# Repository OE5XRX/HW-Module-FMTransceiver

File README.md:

# HW-Module-Template

## Description

This repository is a template for hardware modules using KiCad, designed for clean, maintainable development with CI/CD pipelines generating and publishing production data automatically.

## Features
* Structured KiCad project (schematic, PCB)
* Clean repository: no production data stored
* GitHub Actions CI/CD pipeline:
  * Generates Gerber, BOM, and assembly files
  * Uploads artifacts to GitHub Releases
* Open Hardware license ready (CERN-OHL-S)

## Repository Structure

```
HW-Module-Template/
├── .github/workflows/     # CI/CD pipeline scripts
├── doc/                   # Documentation exports
├── symbols/               # Local symbol library (if needed)
├── footprints/            # Local footprint library (if needed)
├── 3d-models/             # STEP/WRL files (optional)
├── main.kicad_pro         # KiCad main project file
├── main.kicad_sch         # KiCad main schematic file
├── main.kicad_pcb         # KiCad main pcb file
├── *.kicad_sch            # other KiCad schematic files
├── LICENSE
└── README.md
```

## Usage
1. Click “Use this template” on GitHub.
2. Clone your repository locally and open in KiCad.
3. fix the missing names in the readme and add documentation in the `doc/index.md` file.
4. Work on your schematic and PCB as usual (create a new project (main-file must be called `main.kicad_*`) or copy a new one into the folder structure).
5. Push your changes.
6. CI/CD will automatically generate production files.
7. If there is a release defined, CI/CD will create a documentation on the main webpage.

## License

This project is licensed under [CERN-OHL-S-2.0](https://choosealicense.com/licenses/cern-ohl-s-2.0/).

## Badges

<br>
<br>
<br>
<br>
<br>

## Contact

OE5XRX Amateur Radio Club<br>
🌐 https://oe5xrx.org<br>
✉️ info@oe5xrx.org<br>

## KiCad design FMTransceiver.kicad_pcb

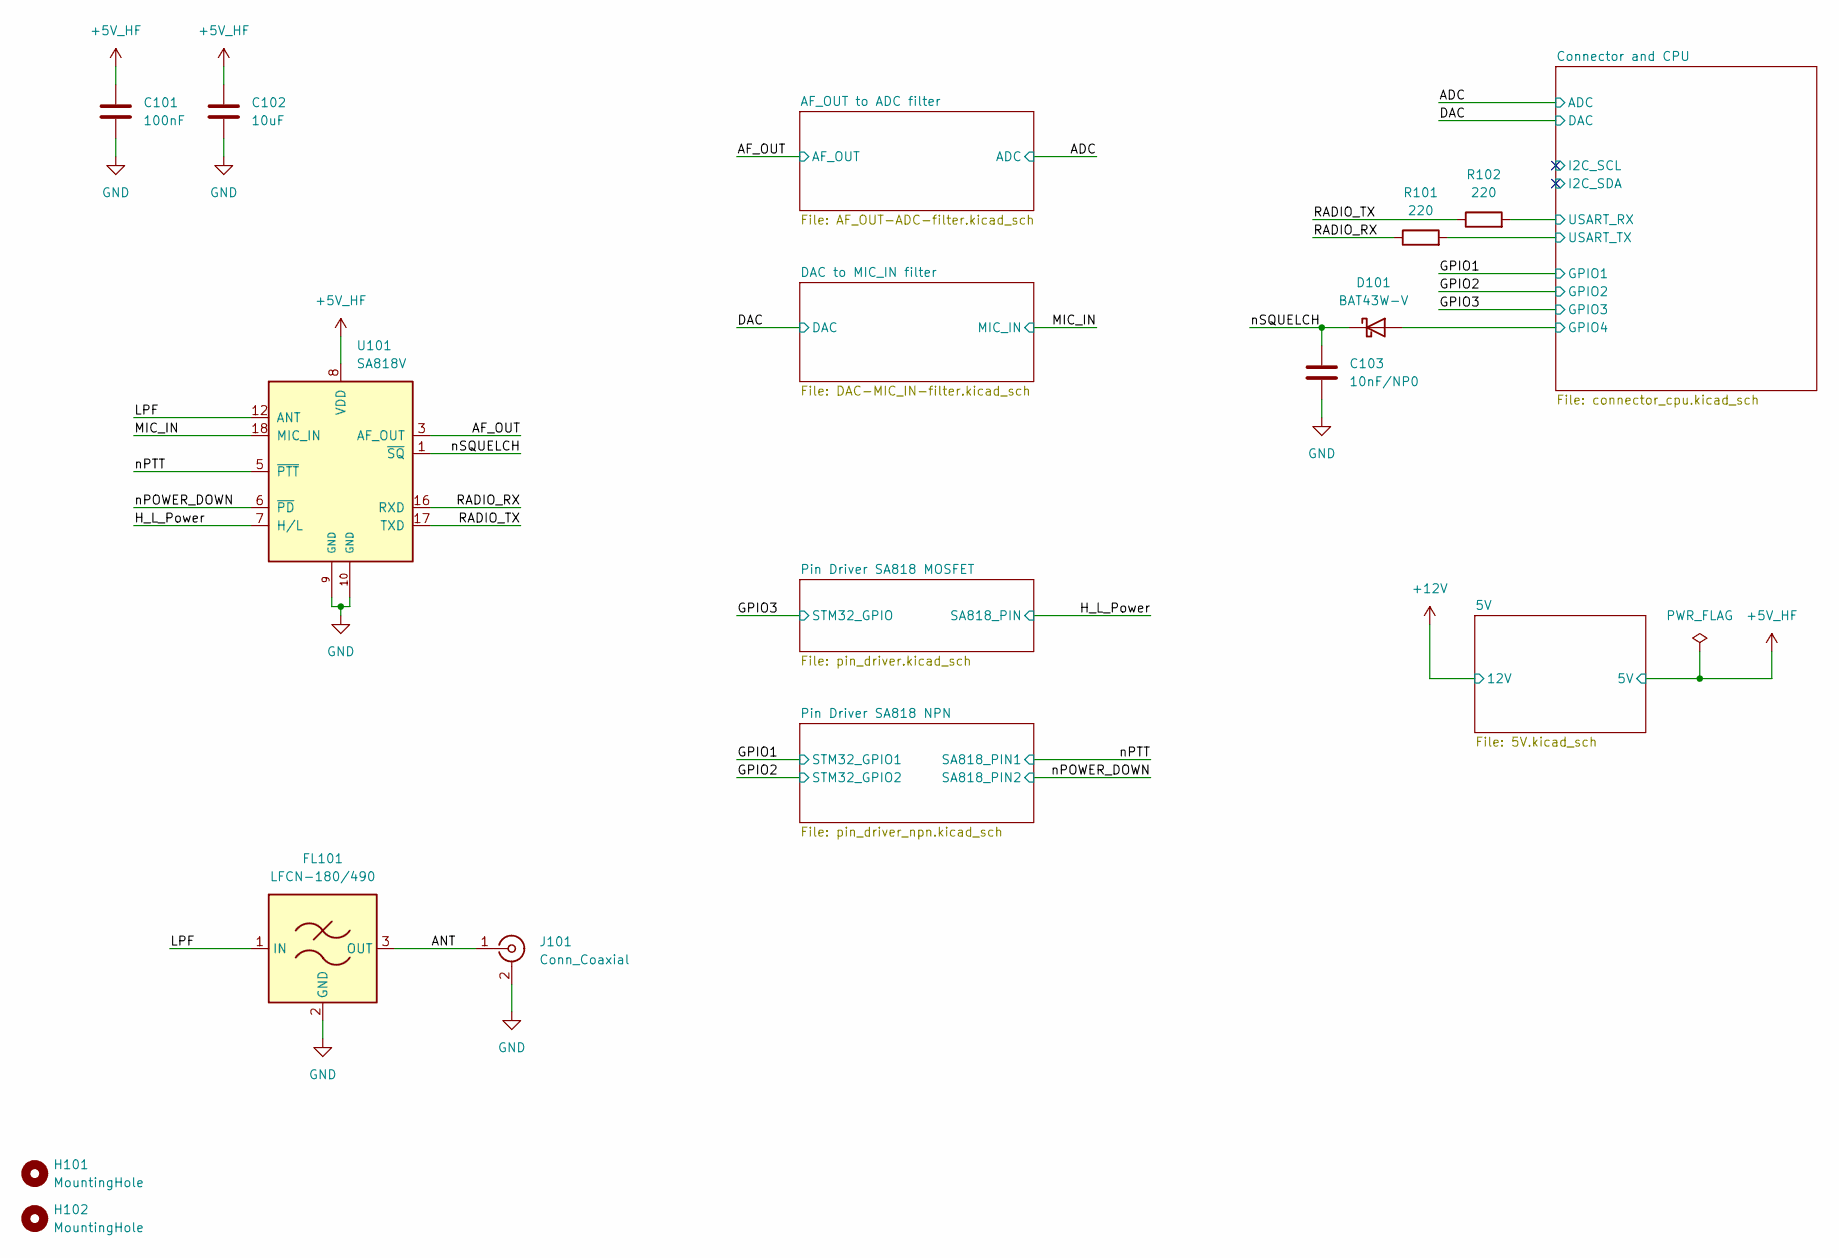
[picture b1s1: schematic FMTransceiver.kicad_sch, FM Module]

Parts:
C101: 100nF; C_0805_2012Metric; LCSC C28233
C102: 10uF; C_0805_2012Metric; MOUSER 963-EMK212BJ106KG-T
C103: 10nF/NP0; C_0805_2012Metric; MOUSER 81-GRM2165C2A103JA1D
D101: BAT43W-V; D_SOD-123; MOUSER 78-BAT43W-G3-08
FL101: LFCN-180/490; Filter_Mini-Circuits_FV1206; MOUSER 139-LFCN-180,139-LFCN-490
H101, H102: MountingHole; MountingHole_3.2mm_M3
J101: Conn_Coaxial; SMA_Amphenol_132289_EdgeMount; MOUSER 530-142-0701-801
R101, R102: 220; R_0805_2012Metric; MOUSER 667-ERA-6AEB221V
U101: SA818V; DRA818; LCSC C3001504

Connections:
+5V_HF: C101.2, C102.2, U101.8 (VDD); also elsewhere on the board
/AF_OUT: U101.3 (AF_OUT); also elsewhere on the board
/ANT: FL101.3 (OUT), J101.1 (In)
/Connector and CPU/GPIO4: D101.2 (A); also elsewhere on the board
/Connector and CPU/USART_RX: R102.2; also elsewhere on the board
/Connector and CPU/USART_TX: R101.2; also elsewhere on the board
/H_L_Power: U101.7 (H/L); also elsewhere on the board
/LPF: FL101.1 (IN), U101.12 (ANT)
/MIC_IN: U101.18 (MIC_IN); also elsewhere on the board
/RADIO_RX: R101.1, U101.16 (RXD)
/RADIO_TX: R102.1, U101.17 (TXD)
/nPOWER_DOWN: U101.6 (~PD); also elsewhere on the board
/nPTT: U101.5 (~PTT); also elsewhere on the board
/nSQUELCH: C103.2, D101.1 (K), U101.1 (~SQ)
GND: C101.1, C102.1, C103.1, FL101.2 (GND), FL101.4 (GND), J101.2 (Ext), U101.9 (GND), U101.10 (GND); also elsewhere on the board

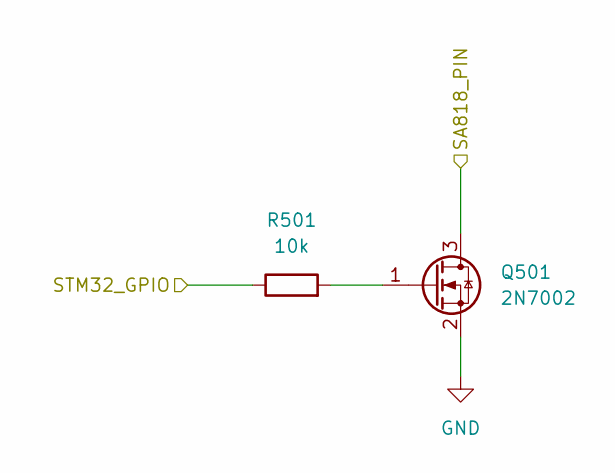
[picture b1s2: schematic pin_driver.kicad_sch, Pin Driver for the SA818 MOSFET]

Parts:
Q501: 2N7002; SOT-23; MOUSER 637-2N7002
R501: 10k; R_0805_2012Metric; MOUSER 603-RT0805DRE0710KL

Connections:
/GPIO3: R501.1; also elsewhere on the board
/H_L_Power: Q501.3 (D); also elsewhere on the board
GND: Q501.2 (S); also elsewhere on the board
unnamed: Q501.1 (G), R501.2

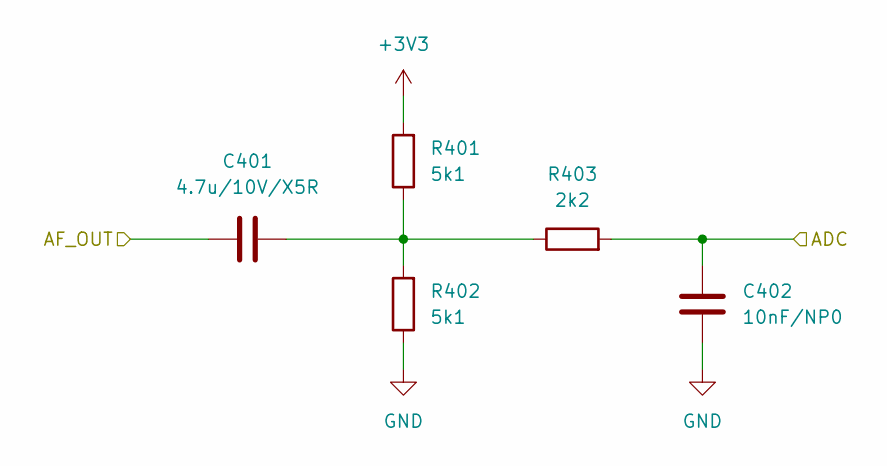
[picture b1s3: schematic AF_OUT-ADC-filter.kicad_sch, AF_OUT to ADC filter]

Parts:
C401: 4.7u/10V/X5R; C_0805_2012Metric; MOUSER 187-CL21A475KAQNNNF
C402: 10nF/NP0; C_0805_2012Metric; MOUSER 81-GRM2165C2A103JA1D
R401, R402: 5k1; R_0805_2012Metric; LCSC C27834
R403: 2k2; R_0805_2012Metric; LCSC C17520

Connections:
+3V3: R401.2; also elsewhere on the board
/ADC: C402.2, R403.2; also elsewhere on the board
/AF_OUT: C401.2; also elsewhere on the board
GND: C402.1, R402.1; also elsewhere on the board
unnamed: C401.1, R401.1, R402.2, R403.1

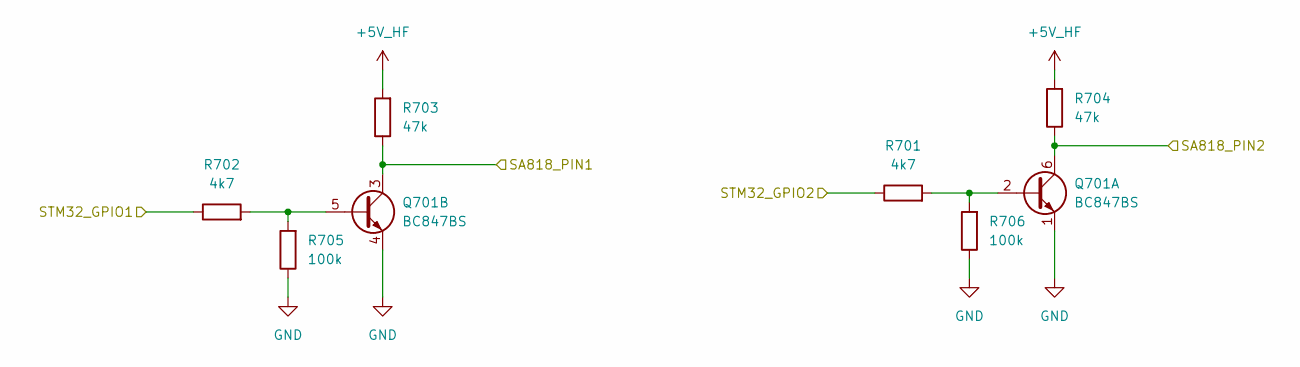
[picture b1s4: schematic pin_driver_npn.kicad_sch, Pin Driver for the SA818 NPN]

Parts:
Q701: BC847BS; SOT-363_SC-70-6; MOUSER 241-BC847BS_R1_00001
R701, R702: 4k7; R_0805_2012Metric; MOUSER 603-RC0805FR-074K7L
R703, R704: 47k; R_0805_2012Metric; MOUSER 603-AC0805FR-1047KL
R705, R706: 100k; R_0805_2012Metric; MOUSER 603-RC0805JR-07100KL

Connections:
+5V_HF: R703.2, R704.2; also elsewhere on the board
/GPIO1: R702.1; also elsewhere on the board
/GPIO2: R701.1; also elsewhere on the board
/nPOWER_DOWN: Q701.6 (C1), R704.1; also elsewhere on the board
/nPTT: Q701.3 (C2), R703.1; also elsewhere on the board
GND: Q701.1 (E1), Q701.4 (E2), R705.1, R706.1; also elsewhere on the board
unnamed: Q701.2 (B1), R701.2, R706.2
unnamed: Q701.5 (B2), R702.2, R705.2

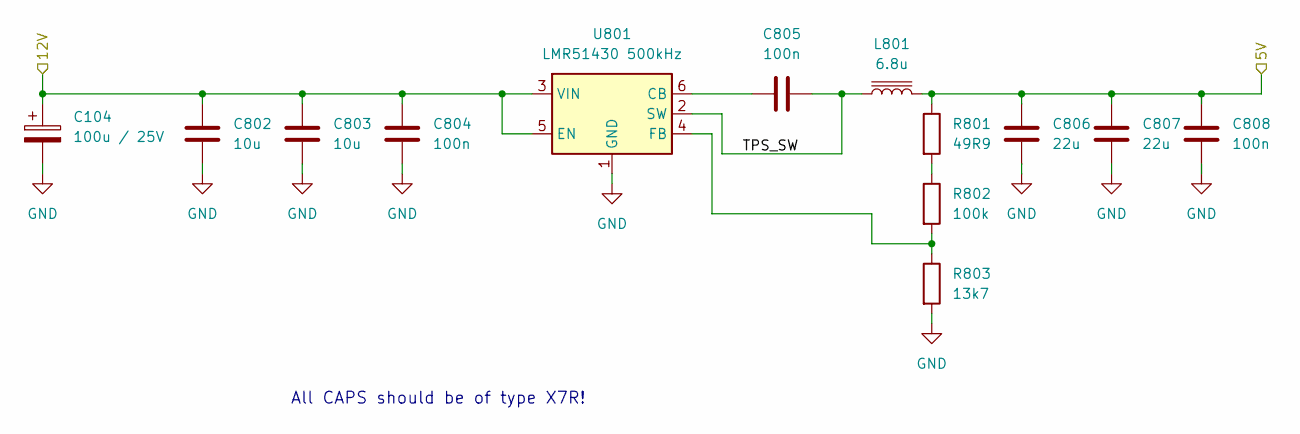
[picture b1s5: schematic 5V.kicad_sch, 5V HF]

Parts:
C104: 100u / 25V; CP_EIA-7343-43_Kemet-X; LCSC C132558
C802, C803: 10u; C_1206_3216Metric; LCSC C13585
C804, C805, C808: 100n; C_0805_2012Metric; LCSC C28233
C806, C807: 22u; C_1206_3216Metric; LCSC C12891
L801: 6.8u; WE-XHMI_6060; MOUSER 710-74439346068
R801: 49R9; R_0805_2012Metric; MOUSER 667-ERA-6AED49R9V
R802: 100k; R_0805_2012Metric; MOUSER 603-RC0805JR-07100KL
R803: 13k7; R_0805_2012Metric; MOUSER 652-CR0805FX-1372ELF
U801: LMR51430 500kHz; SOT-23-6; MOUSER 595-LMR51430XDDCR

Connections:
+5V_HF: C806.2, C807.2, C808.2, L801.2, R801.1; also elsewhere on the board
+12V: C104.1, C802.1, C803.1, C804.1, U801.3 (VIN), U801.5 (EN); also elsewhere on the board
/5V/TPS_SW: C805.2, L801.1, U801.2 (SW)
GND: C104.2, C802.2, C803.2, C804.2, C806.1, C807.1, C808.1, R803.2, U801.1 (GND); also elsewhere on the board
unnamed: R801.2, R802.1
unnamed: C805.1, U801.6 (CB)
unnamed: R802.2, R803.1, U801.4 (FB)

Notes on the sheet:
All CAPS should be of type X7R!

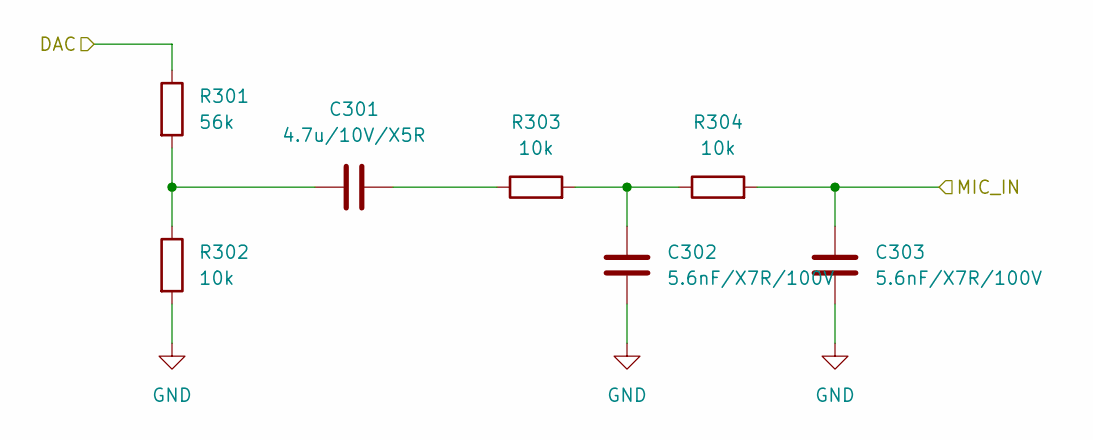
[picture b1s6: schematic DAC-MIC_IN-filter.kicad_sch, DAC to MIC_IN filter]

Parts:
C301: 4.7u/10V/X5R; C_0805_2012Metric; MOUSER 187-CL21A475KAQNNNF
C302, C303: 5.6nF/X7R/100V; C_0805_2012Metric; MOUSER 791-0805B562K201CT
R301: 56k; R_0805_2012Metric; MOUSER 603-RT0805DRE0756KL
R302, R303, R304: 10k; R_0805_2012Metric; MOUSER 603-RT0805DRE0710KL

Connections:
/DAC: R301.1; also elsewhere on the board
/MIC_IN: C303.1, R304.2; also elsewhere on the board
GND: C302.2, C303.2, R302.2; also elsewhere on the board
unnamed: C301.1, R303.1
unnamed: C301.2, R301.2, R302.1
unnamed: C302.1, R303.2, R304.1

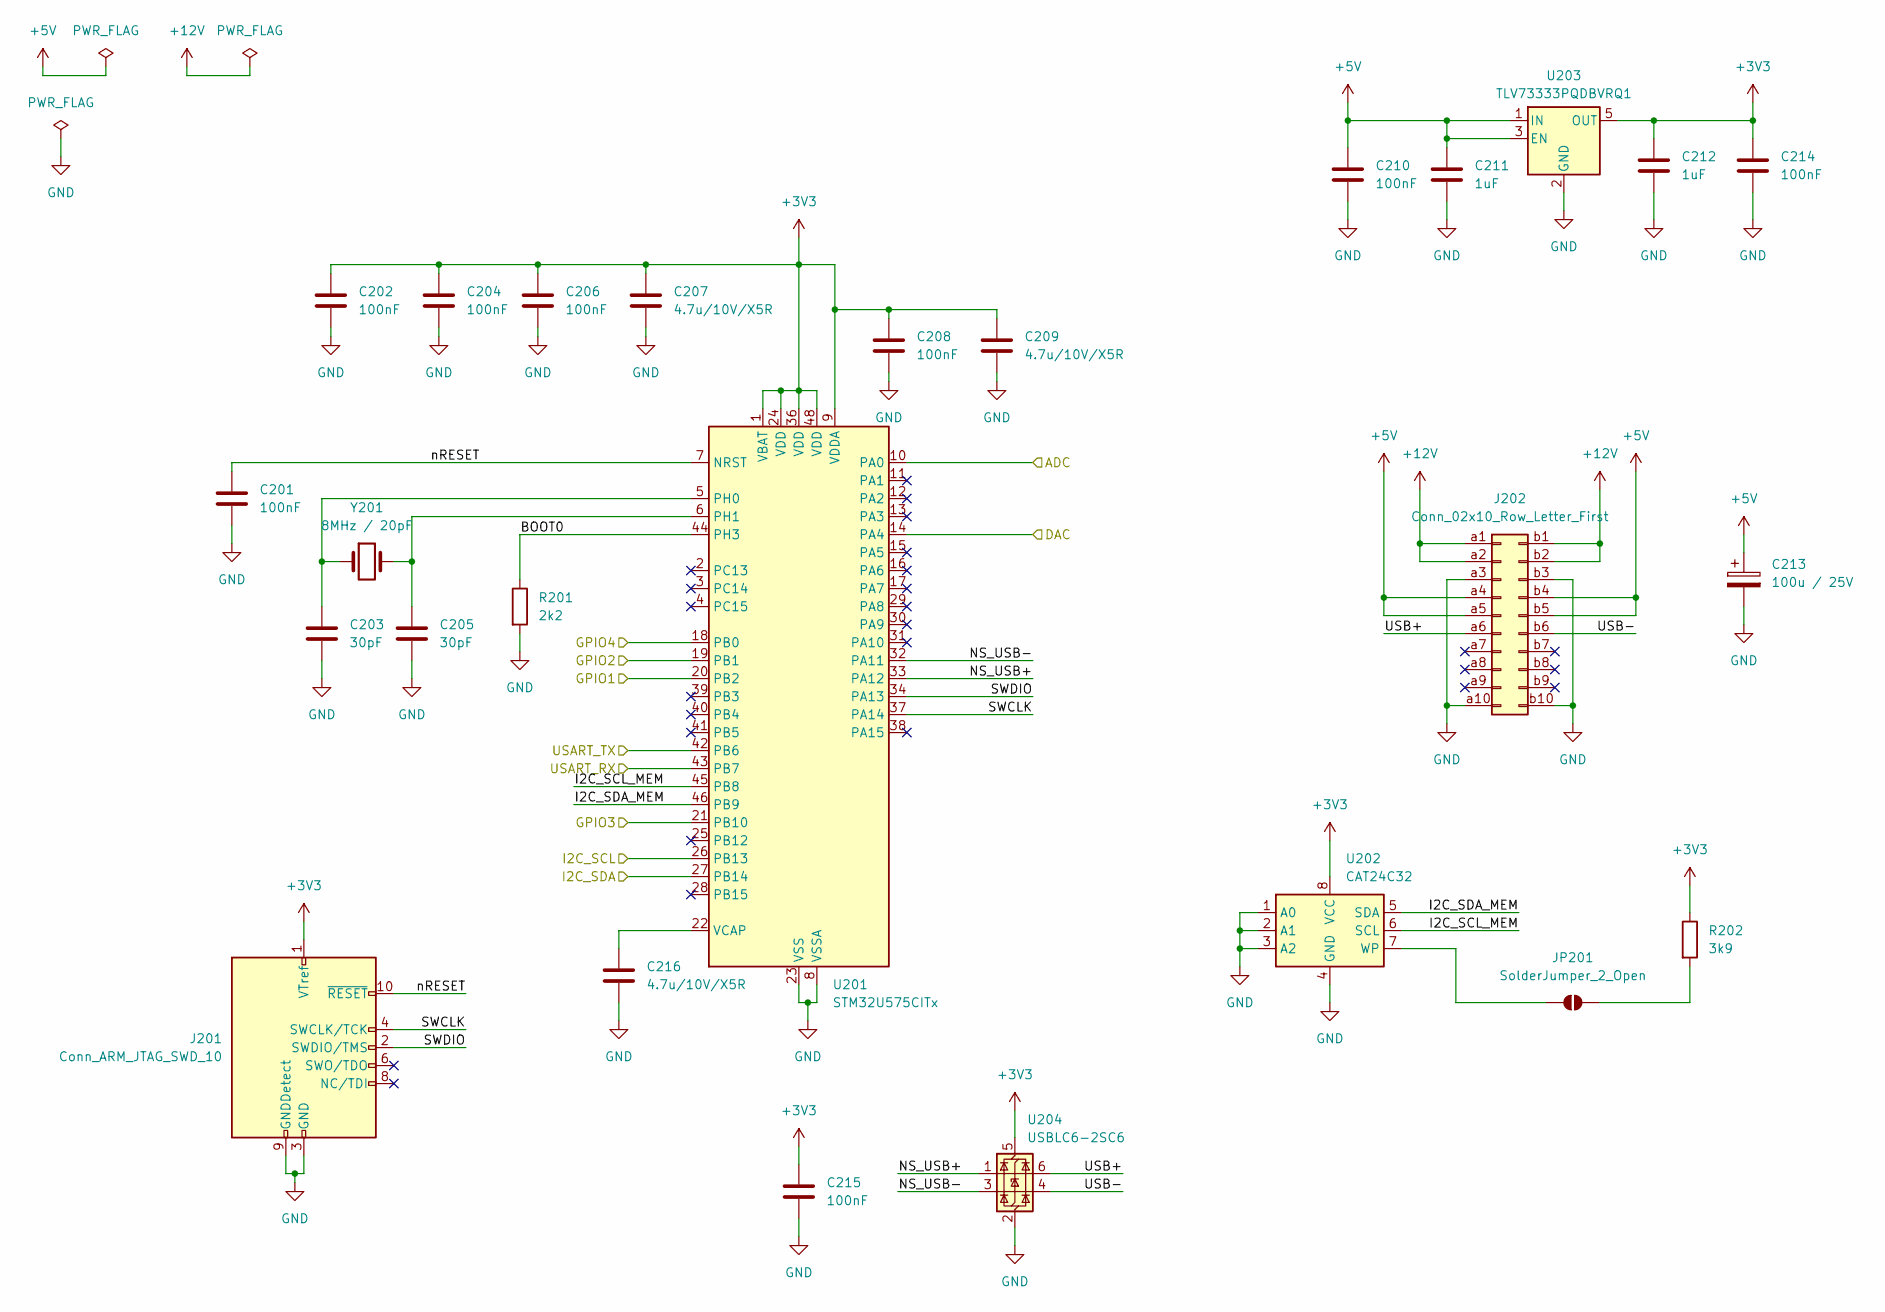
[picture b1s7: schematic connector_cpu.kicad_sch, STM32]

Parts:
C201, C202, C204, C206, C208, C210, C214, C215: 100nF; C_0805_2012Metric; LCSC C28233
C203, C205: 30pF; C_0805_2012Metric; MOUSER 791-0805N300J500CT
C207, C209, C216: 4.7u/10V/X5R; C_0805_2012Metric; MOUSER 187-CL21A475KAQNNNF
C211, C212: 1uF; C_0805_2012Metric; MOUSER 791-0805B105K250CT
C213: 100u / 25V; CP_EIA-7343-43_Kemet-X; LCSC C132558
J201: Conn_ARM_JTAG_SWD_10; PinHeader_2x05_P2.54mm_Horizontal
J202: Conn_02x10_Row_Letter_First; PCN10C-20S-2.54DS; MOUSER 798-PCN10C20S254DS72
JP201: SolderJumper_2_Open; SolderJumper-2_P1.3mm_Open_RoundedPad1.0x1.5mm
R201: 2k2; R_0805_2012Metric; LCSC C17520
R202: 3k9; R_0805_2012Metric; MOUSER 603-RT0805DRD073K9L
U201: STM32U575CITx; LQFP-48_7x7mm_P0.5mm; MOUSER 511-STM32U575CIT6
U202: CAT24C32; SOIC-8_3.9x4.9mm_P1.27mm; MOUSER 698-CAT24C32WI-GT3
U203: TLV73333PQDBVRQ1; SOT-23-5; LCSC C2862550
U204: USBLC6-2SC6; SOT-23-6; LCSC C2827654
Y201: 8MHz / 20pF; Crystal_SMD_HC49-SD; MOUSER 73-XT49M800-20

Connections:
+3V3: C202.2, C204.2, C206.2, C207.2, C208.2, C209.2, C212.1, C214.2, C215.1, J201.1 (VTref), R202.1, U201.1 (VBAT), U201.9 (VDDA), U201.24 (VDD), U201.36 (VDD), U201.48 (VDD), U202.8 (VCC), U203.5 (OUT), U204.5 (VBUS); also elsewhere on the board
+5V: C210.2, C211.1, C213.1, J202.a4, J202.a5, J202.b4, J202.b5, U203.1 (IN), U203.3 (EN)
+12V: J202.a1, J202.a2, J202.b1, J202.b2; also elsewhere on the board
/ADC: U201.10 (PA0); also elsewhere on the board
/Connector and CPU/BOOT0: R201.1, U201.44 (PH3)
/Connector and CPU/GPIO4: U201.18 (PB0); also elsewhere on the board
/Connector and CPU/I2C_SCL: U201.26 (PB13)
/Connector and CPU/I2C_SCL_MEM: U201.45 (PB8), U202.6 (SCL)
/Connector and CPU/I2C_SDA: U201.27 (PB14)
/Connector and CPU/I2C_SDA_MEM: U201.46 (PB9), U202.5 (SDA)
/Connector and CPU/NS_USB+: U201.33 (PA12), U204.1 (I/O1)
/Connector and CPU/NS_USB-: U201.32 (PA11), U204.3 (I/O2)
/Connector and CPU/SWCLK: J201.4 (SWCLK/TCK), U201.37 (PA14)
/Connector and CPU/SWDIO: J201.2 (SWDIO/TMS), U201.34 (PA13)
/Connector and CPU/USART_RX: U201.43 (PB7); also elsewhere on the board
/Connector and CPU/USART_TX: U201.42 (PB6); also elsewhere on the board
/Connector and CPU/USB+: J202.a6, U204.6 (I/O1)
/Connector and CPU/USB-: J202.b6, U204.4 (I/O2)
/Connector and CPU/nRESET: C201.1, J201.10 (~RESET), U201.7 (NRST)
/DAC: U201.14 (PA4); also elsewhere on the board
/GPIO1: U201.20 (PB2); also elsewhere on the board
/GPIO2: U201.19 (PB1); also elsewhere on the board
/GPIO3: U201.21 (PB10); also elsewhere on the board
GND: C201.2, C202.1, C203.2, C204.1, C205.2, C206.1, C207.1, C208.1, C209.1, C210.1, C211.2, C212.2, C213.2, C214.1, C215.2, C216.1, J201.3 (GND), J201.5 (GND), J201.9 (GNDDetect), J202.a3, J202.a10, J202.b3, J202.b10, R201.2, U201.8 (VSSA), U201.23 (VSS), U201.35 (VSS), U201.47 (VSS), U202.1 (A0), U202.2 (A1), U202.3 (A2), U202.4 (GND), U203.2 (GND), U204.2 (GND); also elsewhere on the board
unnamed: JP201.1 (A), U202.7 (WP)
unnamed: JP201.2 (B), R202.2
unnamed: C203.1, U201.5 (PH0), Y201.1
unnamed: C205.1, U201.6 (PH1), Y201.2
unnamed: C216.2, U201.22 (VCAP)

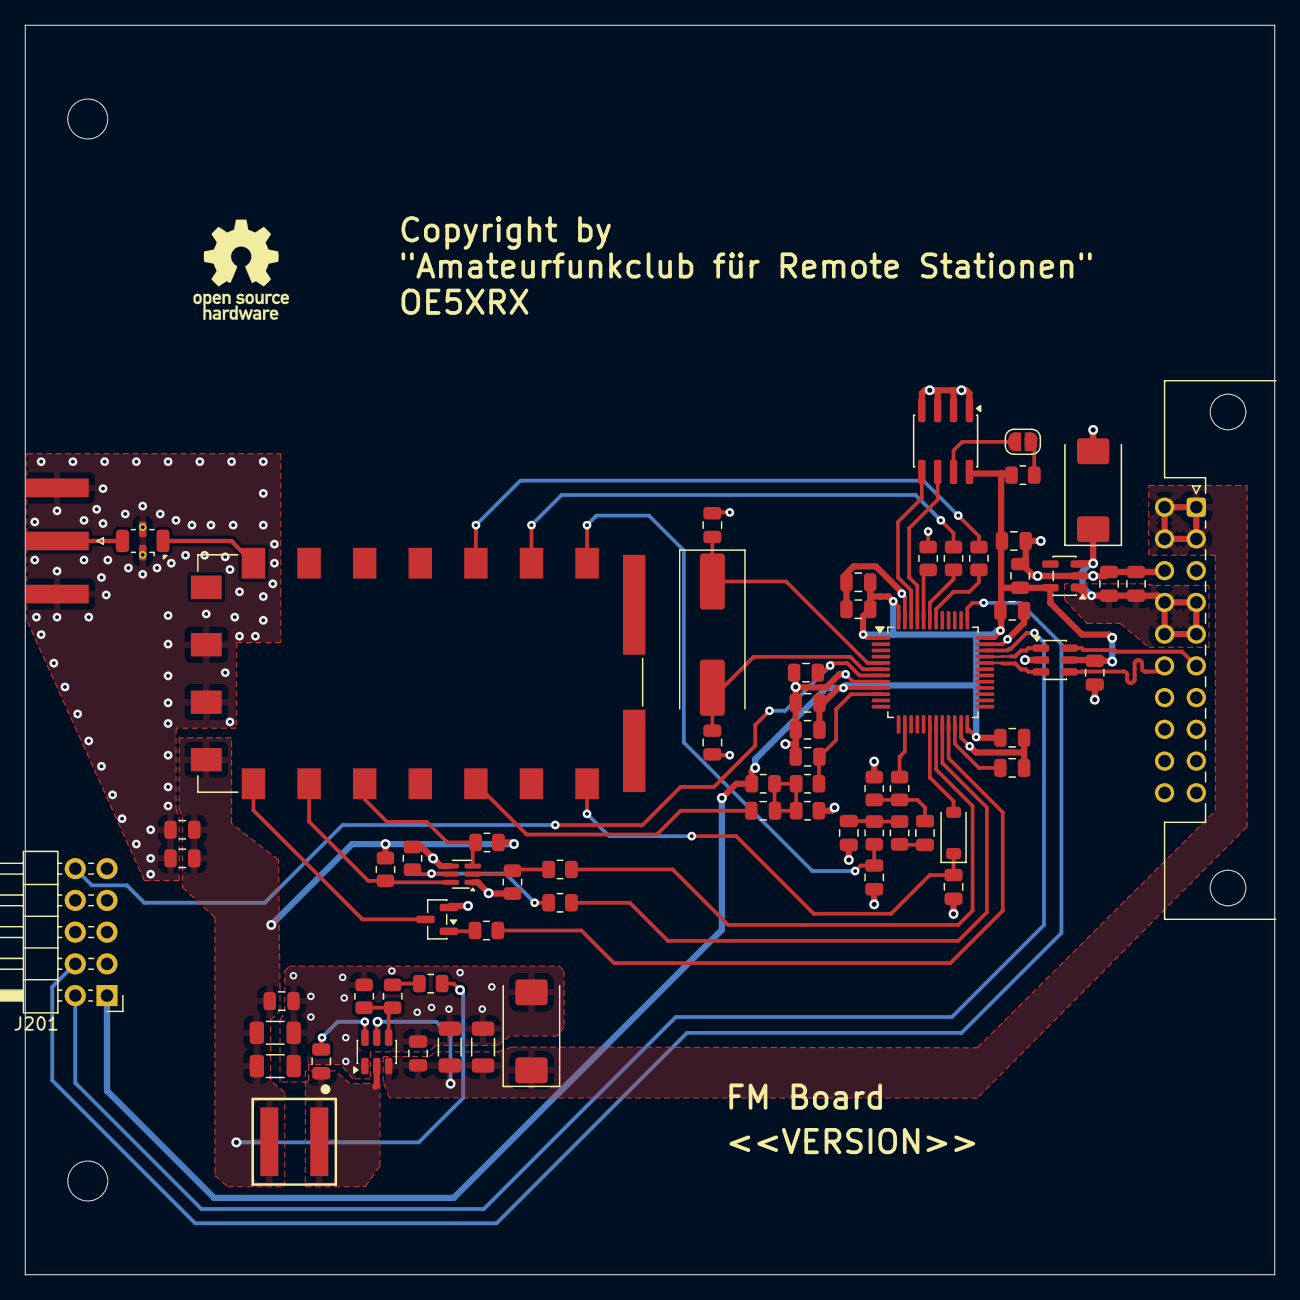
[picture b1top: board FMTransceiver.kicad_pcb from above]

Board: 4 copper layers, 100.0 x 100.0 mm, 71 parts (0 on the bottom side), 49 nets.

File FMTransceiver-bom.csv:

Row,Description,Part,References,Value,Footprint,Quantity Per PCB,Status,Datasheet,LCSC,MOUSER,SnapEDA_Link
1,Unpolarized capacitor,C,C203 C205,30pF,C_0805_2012Metric,2, ,~,,791-0805N300J500CT,
2,Unpolarized capacitor,C,C103 C402,10nF/NP0,C_0805_2012Metric,2, ,~,,81-GRM2165C2A103JA1D,
3,Unpolarized capacitor,C,C101 C201 C202 C204 C206 C208 C210 C214 C215 C804 C805 C808,100nF,C_0805_2012Metric,12, ,~,C28233,,
4,Unpolarized capacitor,C,C211 C212,1uF,C_0805_2012Metric,2, ,~,,791-0805B105K250CT,
5,Unpolarized capacitor,C,C102,10uF,C_0805_2012Metric,1, ,~,,963-EMK212BJ106KG-T,
6,Unpolarized capacitor,C,C802 C803,10u,C_1206_3216Metric,2, ,~,C13585,,
7,Unpolarized capacitor,C,C806 C807,22u,C_1206_3216Metric,2, ,~,C12891,,
8,Polarized capacitor,C_Polarized,C104 C213,100u / 25V,CP_EIA-7343-43_Kemet-X,2, ,~,C132558,,
9,Unpolarized capacitor,C,C207 C209 C216 C301 C401,4.7u/10V/X5R,C_0805_2012Metric,5, ,~,,187-CL21A475KAQNNNF,
10,Unpolarized capacitor,C,C302 C303,5.6nF/X7R/100V,C_0805_2012Metric,2, ,~,,791-0805B562K201CT,
11,"30V 0.2A Small Signal Schottky diode, SOD-123",BAT43W-V,D101,BAT43W-V,D_SOD-123,1, ,http://www.vishay.com/docs/85660/bat42.pdf,,78-BAT43W-G3-08,
12,"180MHz/490MHz 50 Ohm Passive Low Pass Filter, FV1206",LFCN-160,FL101,LFCN-180/490,Filter_Mini-Circuits_FV1206,1, ,https://www.minicircuits.com/pdfs/LFCN-180+.pdf,,"139-LFCN-180,139-LFCN-490",
13,"Generic connector, double row, 02x10, row letter first pin numbering scheme (pin number consists of a letter for the row and a number for the pin index in this row. a1, ..., aN; b1, ..., bN), script generated (kicad-library-utils/schlib/autogen/connector/)",Conn_02x10_Row_Letter_First,J202,Conn_02x10_Row_Letter_First,PCN10C-20S-2.54DS,1, ,~,,798-PCN10C20S254DS72,
14,"Cortex Debug Connector, standard ARM Cortex-M SWD and JTAG interface",Conn_ARM_JTAG_SWD_10,J201,Conn_ARM_JTAG_SWD_10,PinHeader_2x05_P2.54mm_Horizontal,1, ,http://infocenter.arm.com/help/topic/com.arm.doc.ddi0314h/DD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,,,
15,"coaxial connector (BNC, SMA, SMB, SMC, Cinch/RCA, LEMO, ...)",Conn_Coaxial,J101,Conn_Coaxial,SMA_Amphenol_132289_EdgeMount,1, ,~,,530-142-0701-801,
16,Inductor with iron core,L_Iron,L801,6.8u,WE-XHMI_6060,1, ,~,,710-74439346068,
17,"0.115A Id, 60V Vds, N-Channel MOSFET, SOT-23",2N7002,Q501,2N7002,SOT-23,1, ,https://www.onsemi.com/pub/Collateral/NDS7002A-D.PDF,,637-2N7002,
18,"100mA IC, 45V Vce, Dual NPN/NPN Transistors, SOT-363",BC847BS,Q701,BC847BS,SOT-363_SC-70-6,1, ,https://assets.nexperia.com/documents/data-sheet/BC847BS.pdf,,241-BC847BS_R1_00001,
19,Resistor,R,R801,49R9,R_0805_2012Metric,1, ,~,,667-ERA-6AED49R9V,
20,Resistor,R,R101 R102,220,R_0805_2012Metric,2, ,~,,667-ERA-6AEB221V,
21,Resistor,R,R201 R403,2k2,R_0805_2012Metric,2, ,~,C17520,,
22,Resistor,R,R202,3k9,R_0805_2012Metric,1, ,~,,603-RT0805DRD073K9L,
23,Resistor,R,R701 R702,4k7,R_0805_2012Metric,2, ,~,,603-RC0805FR-074K7L,
24,Resistor,R,R401 R402,5k1,R_0805_2012Metric,2, ,~,C27834,,
25,Resistor,R,R302 R303 R304 R501,10k,R_0805_2012Metric,4, ,~,,603-RT0805DRE0710KL,
26,Resistor,R,R803,13k7,R_0805_2012Metric,1, ,~,,652-CR0805FX-1372ELF,
27,Resistor,R,R703 R704,47k,R_0805_2012Metric,2, ,~,,603-AC0805FR-1047KL,
28,Resistor,R,R301,56k,R_0805_2012Metric,1, ,~,,603-RT0805DRE0756KL,
29,Resistor,R,R705 R706 R802,100k,R_0805_2012Metric,3, ,~,,603-RC0805JR-07100KL,
30,"32 kb CMOS Serial EEPROM, SOIC-8/TSSOP-8/DFN-8",CAT24C128,U202,CAT24C32,SOIC-8_3.9x4.9mm_P1.27mm,1, ,,,698-CAT24C32WI-GT3,
31,"4.5-V to 36-V, 3-A synchronous buck converter with 40-µA IQ, SOT-23-6",LMR51430,U801,LMR51430 500kHz,SOT-23-6,1, ,https://www.ti.com/lit/ds/symlink/lmr51430.pdf,,595-LMR51430XDDCR,
32,,SA818V,U101,SA818V,DRA818,1, ,,C3001504,,
33,"STMicroelectronics Arm Cortex-M33 MCU, 2048KB flash, 786KB RAM, 160 MHz, 1.71-3.6V, 37 GPIO, LQFP48",STM32U575CITx,U201,STM32U575CITx,LQFP-48_7x7mm_P0.5mm,1, ,https://www.st.com/resource/en/datasheet/stm32u575ci.pdf,,511-STM32U575CIT6,
34,"300mA Capacitor-Free Low Dropout Voltage Regulator, Fixed Output 3.3V, SOT-23-5",TLV73333PDBV,U203,TLV73333PQDBVRQ1,SOT-23-5,1, ,http://www.ti.com/lit/ds/symlink/tlv733p.pdf,C2862550,595-TLV73333PQDBVRQ1,
35,"Very low capacitance ESD protection diode, 2 data-line, SOT-23-6",USBLC6-2SC6,U204,USBLC6-2SC6,SOT-23-6,1, ,https://www.st.com/resource/en/datasheet/usblc6-2.pdf,C2827654,,
36,Two pin crystal,Crystal,Y201,8MHz / 20pF,Crystal_SMD_HC49-SD,1, ,~,,73-XT49M800-20,

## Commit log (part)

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2025-08-28 setup project
2025-08-31 create gh pages local
2025-08-31 fix wrong doc path
2025-08-31 add missing files
2025-08-31 Initial gh-pages commit
2025-08-31 Deploying to gh-pages from @ 72c39a79c8d3998bdb159b7a3eb7ef7734bba760 🚀
2025-08-31 move into two steps
2025-08-31 add missing v
2025-08-31 Deploying to gh-pages from @ OE5XRX/HW-Module-FMTransceiver@99b11d100822dbe256c55fec0f0cb076ac2616b8 🚀
2025-08-31 fix download path
2025-08-31 Deploying to gh-pages from @ OE5XRX/HW-Module-FMTransceiver@4d0bf9bd00ce79e82b417ac33b3c08975b30440a 🚀
2025-09-01 correct name of action
2025-09-01 Deploying to gh-pages from @ OE5XRX/HW-Module-FMTransceiver@e4283e592f469ee6553a58dc9feb626aaacb76b2 🚀
2026-02-17 update stm32, add some new 3d files
2026-02-17 Deploying to gh-pages from @ OE5XRX/HW-Module-FMTransceiver@269ff037dfbeca4944b0e6215d2f75a681f863ff 🚀
2026-02-17 Deploying to gh-pages from @ OE5XRX/HW-Module-FMTransceiver@1e988fd078c5ecb207761e0f7ae66b82820ca6be 🚀
2026-02-17 fix pcb gnd
2026-02-17 Deploying to gh-pages from @ OE5XRX/HW-Module-FMTransceiver@4e9a404ce012161babd9c13263d47a6320c0a2d9 🚀
2026-02-17 add mouser part numbers
2026-02-17 Deploying to gh-pages from @ OE5XRX/HW-Module-FMTransceiver@6ed5baa787a801a3cf4267704f5dbd739e9c0f9d 🚀
2026-02-18 lets test InvenTree upload
2026-02-18 Deploying to gh-pages from @ OE5XRX/HW-Module-FMTransceiver@2f089955f05ab85acfbbd5a991f80f9490a80b12 🚀
2026-02-19 update InvenTree export
2026-02-19 generate Stencil PNG in debug too
2026-02-19 Deploying to gh-pages from @ OE5XRX/HW-Module-FMTransceiver@1d7e7e97365f2a5f912c2a8a22d25c8e5fed4417 🚀
2026-02-19 use cairosvg to read svg
2026-02-19 fix permissions
2026-02-19 Deploying to gh-pages from @ OE5XRX/HW-Module-FMTransceiver@b0452bf05dd2b6b4aca80d8738d0a7033f4e8851 🚀
2026-02-19 Initial plan
2026-02-19 refactor: split InvenTree sync scripts into inventree_sync package
2026-02-19 feat: externalize category map to YAML file with --categories parameter
2026-02-20 fix: remove hardcoded supplier PKs; warn on unknown KiCad symbols in category map
2026-02-20 Uncomment deploy step in GitHub Actions workflow
2026-02-20 Deploying to gh-pages from @ OE5XRX/HW-Module-FMTransceiver@1a66eba372123f7b49b090239d6fbfcac66d0db8 🚀
2026-02-20 Deploying to gh-pages from @ OE5XRX/HW-Module-FMTransceiver@3f53d761659df946de4d3f191d9492a7b15f1460 🚀
2026-05-11 Fix transistor symbol visibility and update polyline coordinates in schematic
2026-05-11 kicad update to 9.0.8
2026-05-11 Deploying to gh-pages from @ OE5XRX/HW-Module-FMTransceiver@ba4633e95e9cb59e3bc825086a8b34ad6665e2cf 🚀
2026-05-11 refactor(ci): replace workflows with HW-Module-CI thin wrappers
2026-05-11 chore(ci): delete files now provided by HW-Module-CI
2026-05-11 feat(docs): migrate index.md to Jekyll Liquid for output paths
2026-05-11 chore: ignore CI-generated doc/_data/project.yml
2026-05-11 rename(kicad): main.kicad_* -> FMTransceiver.kicad_*
    Distinguishable KiCad window titles on the desktop. The composite action
    in HW-Module-CI auto-detects the project name from the basename of
    *.kicad_pro, so CI behaviour is identical before and after — only the
    artefact filenames change (main-bom.html -> FMTransceiver-bom.html etc.),
    which doc/index.md already routes through {{ site.data.project.name }}.
    Internal references updated:
2026-05-11 Deploying to gh-pages from @ OE5XRX/HW-Module-FMTransceiver@797899211740af0356cbd2441ede6bc0fbb81006 🚀
2026-05-11 Deploying to gh-pages from @ OE5XRX/HW-Module-FMTransceiver@9ed953aeaa99594262e8f9b7e90b4eec03cfa360 🚀
2026-05-13 docs: rewrite FM Transceiver index.md with full architecture overview
    Adds:
    - 1-sentence description front-matter (band-agnostic — 2 m or 70 cm)
    - Übersicht clarifying USB-only CM4 communication via STM32U575
    Composite Device (UAC2 + CDC ACM + DFU)
    - Mermaid block diagram of the signal flow STM32 ↔ SA818 ↔ antenna
    - Band-variant table (SA818V + LFCN-160 for 2 m; SA818U + LFCN-180+490
2026-05-13 fix(docs): correct LPF filter spec — single FV1206 footprint (FL101), LFCN-180 for 2m / LFCN-490 for 70cm
    User correction:
    - 2m needs LFCN-180 (not LFCN-160 as I had — LFCN-160 doesn't even exist)
    - 70cm needs LFCN-490
    - Only ONE filter footprint on the board (FL101, FV1206) — not two
    The 'LFCN-160' value string I'd seen in the schematic only appears as a
    stale Value-property on the SA818 lib_symbol entry (copy-paste leftover
2026-05-13 docs(fm): address Copilot review findings
    7 issues from Copilot's review on PR #14, all valid after schematic
    + PCB verification:
    1. J201 (SWD-Header): 2.54 mm 2x5 horizontal pin header per PCB
    footprint Connector_PinHeader_2.54mm:PinHeader_2x05_P2.54mm_Horizontal,
    NOT 1.27 mm ARM-Cortex-Debug. Need 2.54 mm SWD adapter or per-pin
    jumper wires.
2026-05-13 Deploying to gh-pages from @ OE5XRX/HW-Module-FMTransceiver@7a671f785abe3d10aefa8df506c9ec575a1a91c0 🚀
2026-05-15 Deploying to gh-pages from @ OE5XRX/HW-Module-FMTransceiver@eeb3879f104efedd4878d3a13259d37535001ced 🚀
2026-05-15 Deploying to gh-pages from @ OE5XRX/HW-Module-FMTransceiver@d98c980304938c82d4bfd190f512e48b0add1791 🚀

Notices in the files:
FMTransceiver.kicad_pcb:
Copyright by
{dblquote}Amateurfunkclub für Remote Stationen{dblquote}
README.md:
License: CERN-OHL-S
